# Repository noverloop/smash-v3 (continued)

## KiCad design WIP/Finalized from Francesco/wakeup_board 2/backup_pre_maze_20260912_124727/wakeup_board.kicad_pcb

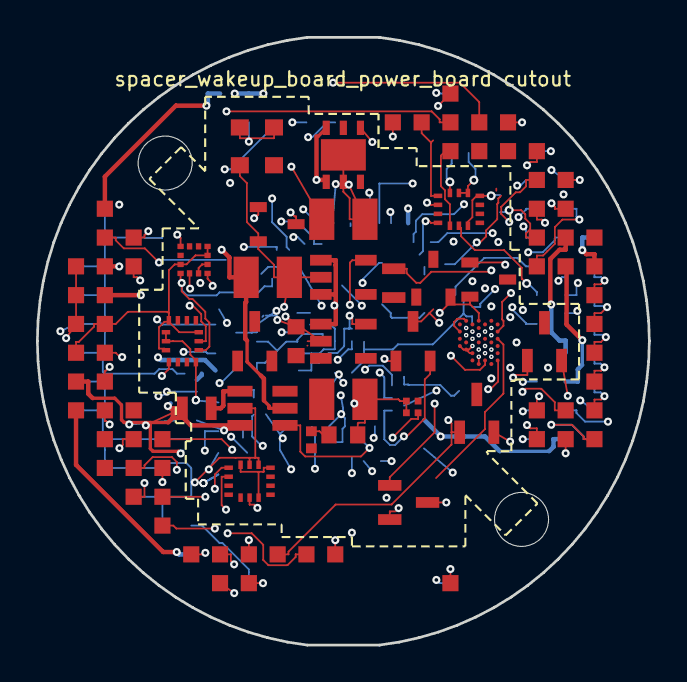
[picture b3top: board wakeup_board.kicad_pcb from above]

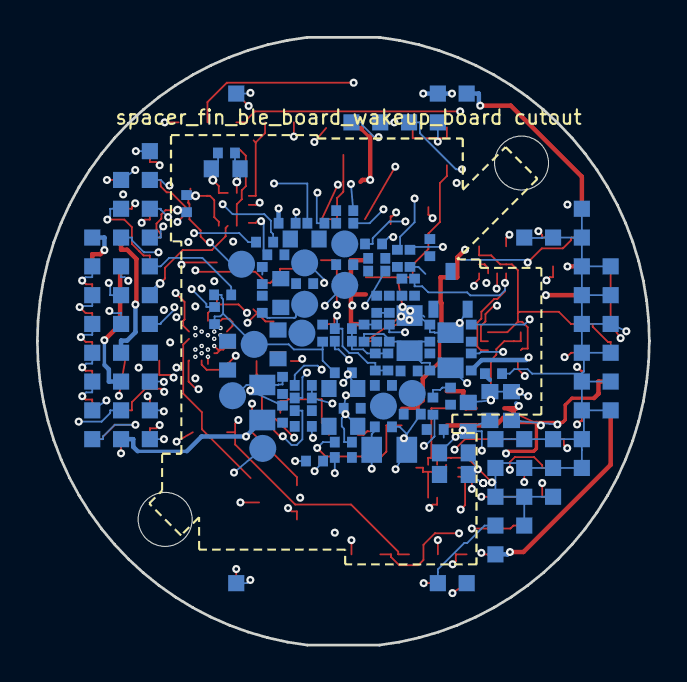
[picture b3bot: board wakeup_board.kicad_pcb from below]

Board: 14 copper layers, 34.0 x 33.8 mm, 112 parts (84 on the bottom side), 85 nets.

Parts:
CBOOST_IN1_1, CBOOST_IN1_2, CBOOST_IN1_3, CBOOST_IN1_4, CBOOST_IN1_5: C-Series MIL-PRF-32535 X7R 0603 2.2uF; Capacitor_SMD_C_0603_1608Metric
CBOOST_IN2: C0402 X7R 100nF; Capacitor_SMD_C_0402_1005Metric
CBOOST_OUT1: T491T 22uF (3528-12 thinnest variant); Capacitor_Tantalum_SMD_CP_EIA-3528-12_Kemet-T
CBOOST_OUT2: C0402 X7R 100nF; Capacitor_SMD_C_0402_1005Metric
CMAIN_HOLD: C0402 X7R 100nF; Capacitor_SMD_C_0402_1005Metric
COUT1, COUT2: T491T 22uF (3528-12 thinnest variant); Capacitor_Tantalum_SMD_CP_EIA-3528-12_Kemet-T
COUT3: C0402 X7R 100nF; Capacitor_SMD_C_0402_1005Metric
C_AON_IN: C-Series MIL-PRF-32535 X7R 0805 1uF; Capacitor_SMD_C_0805_2012Metric
C_AON_OUT: C-Series MIL-PRF-32535 X7R 0805 1uF; Capacitor_SMD_C_0805_2012Metric
C_CAM_VDD: C0402 X7R 100nF; Capacitor_SMD_C_0402_1005Metric
C_IMU1_1, C_IMU2_1, C_IMU3_1: C0402 X7R 100nF; Capacitor_SMD_C_0402_1005Metric
C_IMU1_2, C_IMU2_2, C_IMU3_2: C-Series MIL-PRF-32535 X7R 0603 2.2uF; Capacitor_SMD_C_0603_1608Metric
C_IMU1_3, C_IMU2_3, C_IMU3_3: C0402 X7R 10nF; Capacitor_SMD_C_0402_1005Metric
C_IR_WAKE: C0402 X7R 10nF; Capacitor_SMD_C_0402_1005Metric
C_MAG1: C0402 X7R 100nF; Capacitor_SMD_C_0402_1005Metric
C_MAG2: C-Series MIL-PRF-32535 X7R 0805 1uF; Capacitor_SMD_C_0805_2012Metric
C_MAG_C1: C-Series MIL-PRF-32535 X7R 0603 220nF; Capacitor_SMD_C_0603_1608Metric
C_MAG_SHELF: C0402 X7R 100nF; Capacitor_SMD_C_0402_1005Metric
C_MAG_WAKE: C0402 X7R 100nF; Capacitor_SMD_C_0402_1005Metric
C_TMR_LDO: C-Series MIL-PRF-32535 X7R 0805 1uF; Capacitor_SMD_C_0805_2012Metric
C_WBA_BULK_1, C_WBA_BULK_2: C-Series MIL-PRF-32535 X7R 0603 2.2uF; Capacitor_SMD_C_0603_1608Metric
C_WBA_HSE_VDD: C0402 X7R 100nF; Capacitor_SMD_C_0402_1005Metric
C_WBA_NRST: C0402 X7R 100nF; Capacitor_SMD_C_0402_1005Metric
C_WBA_PI1, C_WBA_PI2: SQCSVA 0.5pF; Capacitor_SMD_C_0603_1608Metric
C_WBA_VDD1, C_WBA_VDD2: C0402 X7R 100nF; Capacitor_SMD_C_0402_1005Metric
C_WBA_VDD11: C-Series MIL-PRF-32535 X7R 0603 2.2uF; Capacitor_SMD_C_0603_1608Metric
C_WBA_VDDA: C0402 X7R 100nF; Capacitor_SMD_C_0402_1005Metric
C_WBA_VDDANA: C0402 X7R 100nF; Capacitor_SMD_C_0402_1005Metric
C_WBA_VDDHPA: C0402 X7R 100nF; Capacitor_SMD_C_0402_1005Metric
C_WBA_VDDRF: C0402 X7R 100nF; Capacitor_SMD_C_0402_1005Metric
C_WBA_VDDRFPA: C0402 X7R 100nF; Capacitor_SMD_C_0402_1005Metric
C_WBA_VDDSMPS: C0402 X7R 100nF; Capacitor_SMD_C_0402_1005Metric
D_AON_WAKE: BAT64-06-TP; SOT95P237X125-3N
D_JUMP_WAKE: BAT64-06-TP; SOT95P237X125-3N
J_wakeup_board_spacer_wakeup_board_power_board: LGA_lands; J_wakeup_board_spacer_wakeup_board_power_board
L_PWR: TMS201210ALM-2R2MTAA; Inductor_SMD_L_2012_2.0x1.25mm
L_WBA_PI: WE-KI 0402 2.7nH (74479xxxxx family); Inductor_SMD_L_0402_1005Metric
L_WBA_SMPS: TMS201210ALM-2R2MTAA; Inductor_SMD_L_2012_2.0x1.25mm
P_wakeup_board_spacer_fin_ble_board_wakeup_board: LGA_lands; P_wakeup_board_spacer_fin_ble_board_wakeup_board
QHOLD, QHOLD2: BSS138LT1G; SOT96P237X111-3N
QMAIN: IRLML6402TRPBF; SOT95P237X112-3N
Q_AON_EN: IRLML6402TRPBF; SOT95P237X112-3N
Q_USB_WAKE2: BSS138LT1G; SOT96P237X111-3N
Q_WBA_RST: BSS138LT1G; SOT96P237X111-3N
RAON_PU: CRCW0402 1M 1% e3; Resistor_SMD_R_0402_1005Metric
RHOLD2_G: CRCW0402 100 1% e3; Resistor_SMD_R_0402_1005Metric
RHOLD2_PD: CRCW0402 100k 1% e3; Resistor_SMD_R_0402_1005Metric
RHOLD_AON: CRCW0402 1k 1% e3; Resistor_SMD_R_0402_1005Metric
RHOLD_G: CRCW0402 100 1% e3; Resistor_SMD_R_0402_1005Metric
RHOLD_PD: CRCW0402 100k 1% e3; Resistor_SMD_R_0402_1005Metric
RMAIN_PU: CRCW0402 1M 1% e3; Resistor_SMD_R_0402_1005Metric
RPU_I2C2_SCL, RPU_I2C2_SDA, RPU_I2C3_SCL, RPU_I2C3_SDA: CRCW0402 4.7k 1% e3; Resistor_SMD_R_0402_1005Metric
RPU_IR_WAKE: CRCW0402 470k 1% e3; Resistor_SMD_R_0402_1005Metric
RPU_MAG_WAKE: CRCW0402 1M 1% e3; Resistor_SMD_R_0402_1005Metric
RPU_SCL_EXT: CRCW0402 4.7k 1% e3; Resistor_SMD_R_0402_1005Metric
RPU_SDA_EXT: CRCW0402 4.7k 1% e3; Resistor_SMD_R_0402_1005Metric
R_BOOST_FB1: CRCW0402 220k 1% e3; Resistor_SMD_R_0402_1005Metric
R_BOOST_FB2: CRCW0402 100k 1% e3; Resistor_SMD_R_0402_1005Metric
R_IMU1_SCX_PU, R_IMU1_SDX_PU, R_IMU2_SCX_PU, R_IMU2_SDX_PU, R_IMU3_SCX_PU, R_IMU3_SDX_PU: CRCW0402 10k 1% e3; Resistor_SMD_R_0402_1005Metric
R_JUMP_PU: CRCW0402 22k 1% e3; Resistor_SMD_R_0402_1005Metric
R_JUMP_WAKE: CRCW0402 3.3k 1% e3; Resistor_SMD_R_0402_1005Metric
R_MAG_SHELF: CRCW0402 3.3k 1% e3; Resistor_SMD_R_0402_1005Metric
R_WBARST_PD: CRCW0402 100k 1% e3; Resistor_SMD_R_0402_1005Metric
R_WBA_BOOT0: CRCW0402 10k 1% e3; Resistor_SMD_R_0402_1005Metric
R_WBA_NRST: CRCW0402 10k 1% e3; Resistor_SMD_R_0402_1005Metric
R_WILK_ISO: CRCW0402 100 1% e3; Resistor_SMD_R_0402_1005Metric
TP_3V3: TP_3V3; TestPoint_TestPoint_Pad_D1.5mm
TP_BAT: TP_BAT; TestPoint_TestPoint_Pad_D1.5mm
TP_GND: TP_GND; TestPoint_TestPoint_Pad_D1.5mm
TP_IMU1_INT: TP_IMU1_INT; TestPoint_TestPoint_Pad_D1.5mm
TP_IMU2_INT: TP_IMU2_INT; TestPoint_TestPoint_Pad_D1.5mm
TP_IMU3_INT: TP_IMU3_INT; TestPoint_TestPoint_Pad_D1.5mm
TP_MAG_DRDY: TP_MAG_DRDY; TestPoint_TestPoint_Pad_D1.5mm
TP_WILK_A: TP_WILK_A; TestPoint_TestPoint_Pad_D1.5mm
TP_WILK_B: TP_WILK_B; TestPoint_TestPoint_Pad_D1.5mm
TP_YAGI_RF_A: TP_YAGI_RF_A; TestPoint_TestPoint_Pad_D1.5mm
TP_YAGI_RF_B: TP_YAGI_RF_B; TestPoint_TestPoint_Pad_D1.5mm
U_AON_LDO: TPS7A0233PDBVR; SOT95P280X145-5N
U_BOOST: MCP1640CT-I/CHY; SOT95P270X145-6N
U_IMU1, U_IMU2, U_IMU3: ISM330DHCXTR; LSM6DS3USTR (LGA-14)
U_MAG: IIS2MDCTR
U_MAG_SHELF: RR123-1H02-612
U_MAG_WAKE: SOT95P237X112-3N
U_PWR: LDL112PV33R; SON95P300X300X100-7N-D
U_TMR_LDO: TPS7A0233PDBVR; SOT95P280X145-5N
U_WBA: STM32WBA55HGF6TR; BGA41C35P13X7_298X276X50
Y_WBA_HSE: DSC1001CI5-032.0000; DSC1001CI50080000

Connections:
3V3: COUT1.1, COUT2.1, COUT3.1, C_IMU1_1.1, C_IMU1_2.1, C_IMU1_3.1, C_IMU2_1.1, C_IMU2_2.1, C_IMU2_3.1, C_IMU3_1.1, C_IMU3_2.1, C_IMU3_3.1, C_MAG1.1, C_MAG2.1, J_wakeup_board_spacer_wakeup_board_powe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.1, J_wakeup_board_spacer_wakeup_board_powe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.55, J_wakeup_board_spacer_wakeup_board_powe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.62, P_wakeup_board_spacer_fin_ble_board_wak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.1, P_wakeup_board_spacer_fin_ble_board_wak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.35, P_wakeup_board_spacer_fin_ble_board_wak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.41, RPU_I2C2_SCL.1, RPU_I2C2_SDA.1, RPU_I2C3_SCL.1, RPU_I2C3_SDA.1, RPU_SCL_EXT.1, RPU_SDA_EXT.1, R_IMU1_SCX_PU.1, R_IMU1_SDX_PU.1, R_IMU2_SCX_PU.1, R_IMU2_SDX_PU.1, R_IMU3_SCX_PU.1, R_IMU3_SDX_PU.1, TP_3V3.1, U_IMU1.5, U_IMU1.8, U_IMU1.12, U_IMU2.5, U_IMU2.8, U_IMU2.12, U_IMU3.1, U_IMU3.5, U_IMU3.8, U_IMU3.12, U_MAG.3, U_MAG.9, U_MAG.10, U_PWR.4
3V3_AON: C_AON_OUT.1, C_MAG_WAKE.1, C_WBA_BULK_1.1, C_WBA_BULK_2.1, C_WBA_HSE_VDD.1, C_WBA_VDD1.1, C_WBA_VDD2.1, C_WBA_VDDA.1, C_WBA_VDDANA.1, C_WBA_VDDHPA.1, C_WBA_VDDRF.1, C_WBA_VDDRFPA.1, C_WBA_VDDSMPS.1, P_wakeup_board_spacer_fin_ble_board_wak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.2, P_wakeup_board_spacer_fin_ble_board_wak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.36, RPU_IR_WAKE.1, RPU_MAG_WAKE.1, R_WBA_NRST.1, U_AON_LDO.5, U_MAG_WAKE.1, U_WBA.A6, U_WBA.A10, U_WBA.B5, U_WBA.B13, U_WBA.C4, U_WBA.C6, U_WBA.E12, U_WBA.G4, Y_WBA_HSE.1, Y_WBA_HSE.4
ACTIVATE_CONFIRM: J_wakeup_board_spacer_wakeup_board_powe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.2, P_wakeup_board_spacer_fin_ble_board_wak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.3
ACTIVATE_SET: J_wakeup_board_spacer_wakeup_board_powe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.3, P_wakeup_board_spacer_fin_ble_board_wak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.4
AON_EN: Q_AON_EN.3, RHOLD_AON.2, U_AON_LDO.3
AON_EN_GATE: D_AON_WAKE.3, Q_AON_EN.1, Q_USB_WAKE2.3, RAON_PU.2
BAT_CELL1_POS: J_wakeup_board_spacer_wakeup_board_powe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.4, P_wakeup_board_spacer_fin_ble_board_wak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.5
BAT_CELL2_POS: J_wakeup_board_spacer_wakeup_board_powe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.5, P_wakeup_board_spacer_fin_ble_board_wak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.6
BAT_CELL3_POS: J_wakeup_board_spacer_wakeup_board_powe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.6, P_wakeup_board_spacer_fin_ble_board_wak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.7
BAT_PROT: J_wakeup_board_spacer_wakeup_board_powe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.7, J_wakeup_board_spacer_wakeup_board_powe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.56, P_wakeup_board_spacer_fin_ble_board_wak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.8, P_wakeup_board_spacer_fin_ble_board_wak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.37, QMAIN.2, TP_BAT.1
BAT_RAW: C_AON_IN.1, J_wakeup_board_spacer_wakeup_board_powe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.8, J_wakeup_board_spacer_wakeup_board_powe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.57, P_wakeup_board_spacer_fin_ble_board_wak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.9, P_wakeup_board_spacer_fin_ble_board_wak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.38, Q_AON_EN.2, RAON_PU.1, RMAIN_PU.1, R_JUMP_PU.1, U_AON_LDO.1, U_TMR_LDO.1, U_TMR_LDO.3
BOOST_FB: R_BOOST_FB1.2, R_BOOST_FB2.1, U_BOOST.4
BOOST_OUT: CBOOST_OUT1.1, CBOOST_OUT2.1, R_BOOST_FB1.1, U_BOOST.5, U_PWR.1, U_PWR.6
BOOST_SW: L_PWR.2, U_BOOST.1
BOOT0: J_wakeup_board_spacer_wakeup_board_powe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.9, P_wakeup_board_spacer_fin_ble_board_wak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.10
COMP_1V8: C_CAM_VDD.1, J_wakeup_board_spacer_wakeup_board_powe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.10, J_wakeup_board_spacer_wakeup_board_powe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.58
COMP_5V: J_wakeup_board_spacer_wakeup_board_powe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.11, J_wakeup_board_spacer_wakeup_board_powe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.59, P_wakeup_board_spacer_fin_ble_board_wak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.11, P_wakeup_board_spacer_fin_ble_board_wak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.39
COMP_5V_RAW: J_wakeup_board_spacer_wakeup_board_powe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.12, J_wakeup_board_spacer_wakeup_board_powe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.60, P_wakeup_board_spacer_fin_ble_board_wak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.12, P_wakeup_board_spacer_fin_ble_board_wak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.40
COMP_OUT: J_wakeup_board_spacer_wakeup_board_powe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.13, P_wakeup_board_spacer_fin_ble_board_wak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.13
COMP_SWDCLK: J_wakeup_board_spacer_wakeup_board_powe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.14, P_wakeup_board_spacer_fin_ble_board_wak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.14
COMP_SWDIO: J_wakeup_board_spacer_wakeup_board_powe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.15, P_wakeup_board_spacer_fin_ble_board_wak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.15
EXT_CAN_RX: J_wakeup_board_spacer_wakeup_board_powe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.16, P_wakeup_board_spacer_fin_ble_board_wak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.16
EXT_CAN_TX: J_wakeup_board_spacer_wakeup_board_powe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.17, P_wakeup_board_spacer_fin_ble_board_wak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.17
FLEX_GND: CBOOST_IN1_1.2, CBOOST_IN1_2.2, CBOOST_IN1_3.2, CBOOST_IN1_4.2, CBOOST_IN1_5.2, CBOOST_IN2.2, CBOOST_OUT1.2, CBOOST_OUT2.2, CMAIN_HOLD.2, COUT1.2, COUT2.2, COUT3.2, C_AON_IN.2, C_AON_OUT.2, C_CAM_VDD.2, C_IMU1_1.2, C_IMU1_2.2, C_IMU1_3.2, C_IMU2_1.2, C_IMU2_2.2, C_IMU2_3.2, C_IMU3_1.2, C_IMU3_2.2, C_IMU3_3.2, C_IR_WAKE.2, C_MAG1.2, C_MAG2.2, C_MAG_C1.2, C_MAG_SHELF.2, C_MAG_WAKE.2, C_TMR_LDO.2, C_WBA_BULK_1.2, C_WBA_BULK_2.2, C_WBA_HSE_VDD.2, C_WBA_NRST.2, C_WBA_PI1.2, C_WBA_PI2.2, C_WBA_VDD1.2, C_WBA_VDD2.2, C_WBA_VDD11.2, C_WBA_VDDA.2, C_WBA_VDDANA.2, C_WBA_VDDHPA.2, C_WBA_VDDRF.2, C_WBA_VDDRFPA.2, C_WBA_VDDSMPS.2, J_wakeup_board_spacer_wakeup_board_powe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.18, J_wakeup_board_spacer_wakeup_board_powe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.63, J_wakeup_board_spacer_wakeup_board_powe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.64, J_wakeup_board_spacer_wakeup_board_powe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.65, P_wakeup_board_spacer_fin_ble_board_wak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.18, P_wakeup_board_spacer_fin_ble_board_wak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.42, P_wakeup_board_spacer_fin_ble_board_wak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.43, P_wakeup_board_spacer_fin_ble_board_wak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.44, P_wakeup_board_spacer_fin_ble_board_wak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.45, P_wakeup_board_spacer_fin_ble_board_wak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.46, P_wakeup_board_spacer_fin_ble_board_wak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.47, P_wakeup_board_spacer_fin_ble_board_wak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.48, P_wakeup_board_spacer_fin_ble_board_wak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.49, P_wakeup_board_spacer_fin_ble_board_wak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.50, P_wakeup_board_spacer_fin_ble_board_wak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.51, P_wakeup_board_spacer_fin_ble_board_wak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.52, P_wakeup_board_spacer_fin_ble_board_wak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.53, P_wakeup_board_spacer_fin_ble_board_wak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.54, P_wakeup_board_spacer_fin_ble_board_wak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.55, P_wakeup_board_spacer_fin_ble_board_wak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.56, P_wakeup_board_spacer_fin_ble_board_wak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.57, P_wakeup_board_spacer_fin_ble_board_wak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.58, P_wakeup_board_spacer_fin_ble_board_wak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.59, P_wakeup_board_spacer_fin_ble_board_wak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.60, P_wakeup_board_spacer_fin_ble_board_wak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.61, P_wakeup_board_spacer_fin_ble_board_wak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.62, P_wakeup_board_spacer_fin_ble_board_wak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.63, P_wakeup_board_spacer_fin_ble_board_wak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.64, P_wakeup_board_spacer_fin_ble_board_wak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.65, P_wakeup_board_spacer_fin_ble_board_wak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.66, P_wakeup_board_spacer_fin_ble_board_wak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.67, P_wakeup_board_spacer_fin_ble_board_wak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.68, P_wakeup_board_spacer_fin_ble_board_wak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.69, QHOLD.2, QHOLD2.2, Q_USB_WAKE2.2, Q_WBA_RST.2, RHOLD2_PD.2, RHOLD_PD.2, R_BOOST_FB2.2, R_WBARST_PD.2, R_WBA_BOOT0.2, TP_GND.1, U_AON_LDO.2, U_BOOST.2, U_IMU1.1, U_IMU1.6, U_IMU1.7, U_IMU2.1, U_IMU2.6, U_IMU2.7, U_IMU3.6, U_IMU3.7, U_MAG.6, U_MAG.8, U_MAG_SHELF.1, U_MAG_SHELF.4, U_MAG_WAKE.3, U_PWR.2, U_PWR.7, U_TMR_LDO.2, U_WBA.A12, U_WBA.B9, U_WBA.D1, U_WBA.D3, U_WBA.D5, U_WBA.D13, U_WBA.G6, Y_WBA_HSE.2
GPIO_EXT_0: J_wakeup_board_spacer_wakeup_board_powe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.19, P_wakeup_board_spacer_fin_ble_board_wak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.19
GPIO_EXT_1: J_wakeup_board_spacer_wakeup_board_powe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.20, P_wakeup_board_spacer_fin_ble_board_wak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.20
GPIO_EXT_2: J_wakeup_board_spacer_wakeup_board_powe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.21, P_wakeup_board_spacer_fin_ble_board_wak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.21
GPIO_EXT_3: J_wakeup_board_spacer_wakeup_board_powe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.22, P_wakeup_board_spacer_fin_ble_board_wak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.22
H3LIS_INT1: J_wakeup_board_spacer_wakeup_board_powe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.23, P_wakeup_board_spacer_fin_ble_board_wak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.23
I2C2_SCL: J_wakeup_board_spacer_wakeup_board_powe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.24, RPU_I2C2_SCL.2, U_IMU1.13, U_MAG.1, U_WBA.F3
I2C2_SDA: J_wakeup_board_spacer_wakeup_board_powe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.25, RPU_I2C2_SDA.2, U_IMU1.14, U_MAG.4, U_WBA.G2
I2C3_SCL: J_wakeup_board_spacer_wakeup_board_powe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.26, P_wakeup_board_spacer_fin_ble_board_wak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.24, RPU_I2C3_SCL.2, U_IMU2.13, U_IMU3.13
I2C3_SDA: J_wakeup_board_spacer_wakeup_board_powe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.27, P_wakeup_board_spacer_fin_ble_board_wak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.25, RPU_I2C3_SDA.2, U_IMU2.14, U_IMU3.14
IMU1_INT: J_wakeup_board_spacer_wakeup_board_powe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.28, TP_IMU1_INT.1, U_IMU1.4
IMU1_SCX: R_IMU1_SCX_PU.2, U_IMU1.3
IMU1_SDX: R_IMU1_SDX_PU.2, U_IMU1.2
IMU2_INT: J_wakeup_board_spacer_wakeup_board_powe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.29, TP_IMU2_INT.1, U_IMU2.4
IMU2_SCX: R_IMU2_SCX_PU.2, U_IMU2.3
IMU2_SDX: R_IMU2_SDX_PU.2, U_IMU2.2
IMU3_INT: J_wakeup_board_spacer_wakeup_board_powe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.30, TP_IMU3_INT.1, U_IMU3.4
IMU3_SCX: R_IMU3_SCX_PU.2, U_IMU3.3
IMU3_SDX: R_IMU3_SDX_PU.2, U_IMU3.2
IR_TX: J_wakeup_board_spacer_wakeup_board_powe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.31, U_WBA.D9
IR_WAKE: C_IR_WAKE.1, J_wakeup_board_spacer_wakeup_board_powe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.32, RPU_IR_WAKE.2, U_WBA.E6
JUMP_WAKE: P_wakeup_board_spacer_fin_ble_board_wak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.26, R_JUMP_PU.2, R_JUMP_WAKE.2
JUMP_WAKE_K: D_AON_WAKE.1, D_JUMP_WAKE.1, R_JUMP_WAKE.1
MAG_C1_TERM: C_MAG_C1.1, U_MAG.5
MAG_DRDY: J_wakeup_board_spacer_wakeup_board_powe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.33, TP_MAG_DRDY.1, U_MAG.7
MAG_SHELF_K: D_AON_WAKE.2, D_JUMP_WAKE.2, R_MAG_SHELF.1
MAG_SHELF_N: R_MAG_SHELF.2, U_MAG_SHELF.3
MAG_WAKE_N: RPU_MAG_WAKE.2, U_MAG_WAKE.2, U_WBA.G8
MAIN_SW_GATE: CMAIN_HOLD.1, D_JUMP_WAKE.3, J_wakeup_board_spacer_wakeup_board_powe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.34, QHOLD.3, QHOLD2.3, QMAIN.1, RMAIN_PU.2
NRST: J_wakeup_board_spacer_wakeup_board_powe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.35, P_wakeup_board_spacer_fin_ble_board_wak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.27
PWR_HOLD: J_wakeup_board_spacer_wakeup_board_powe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.36, RHOLD_G.1
QHOLD2_GATE: QHOLD2.1, RHOLD2_G.2, RHOLD2_PD.1
QHOLD_GATE: QHOLD.1, RHOLD_G.2, RHOLD_PD.1
REG_IN_MAIN: CBOOST_IN1_1.1, CBOOST_IN1_2.1, CBOOST_IN1_3.1, CBOOST_IN1_4.1, CBOOST_IN1_5.1, CBOOST_IN2.1, J_wakeup_board_spacer_wakeup_board_powe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.37, J_wakeup_board_spacer_wakeup_board_powe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.61, L_PWR.1, QMAIN.3, U_BOOST.3, U_BOOST.6
SWO: J_wakeup_board_spacer_wakeup_board_powe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.38, P_wakeup_board_spacer_fin_ble_board_wak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.28
SYS_I2C_SCL: J_wakeup_board_spacer_wakeup_board_powe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.39, P_wakeup_board_spacer_fin_ble_board_wak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.29, RPU_SCL_EXT.2
SYS_I2C_SDA: J_wakeup_board_spacer_wakeup_board_powe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.40, P_wakeup_board_spacer_fin_ble_board_wak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.30, RPU_SDA_EXT.2
SYS_SPI_CS_FIN: J_wakeup_board_spacer_wakeup_board_powe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.41, P_wakeup_board_spacer_fin_ble_board_wak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.31
SYS_SPI_MISO: J_wakeup_board_spacer_wakeup_board_powe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.42, P_wakeup_board_spacer_fin_ble_board_wak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.32
SYS_SPI_MOSI: J_wakeup_board_spacer_wakeup_board_powe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.43, P_wakeup_board_spacer_fin_ble_board_wak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.33
SYS_SPI_SCLK: J_wakeup_board_spacer_wakeup_board_powe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.44, P_wakeup_board_spacer_fin_ble_board_wak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.34
TMR_VDD: C_MAG_SHELF.1, C_TMR_LDO.1, U_MAG_SHELF.2, U_TMR_LDO.5
USBWK_GATE: J_wakeup_board_spacer_wakeup_board_powe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.45, Q_USB_WAKE2.1
WBA_AON_HOLD: RHOLD_AON.1, U_WBA.E4
WBA_BOOT0: J_wakeup_board_spacer_wakeup_board_powe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.46, R_WBA_BOOT0.1, U_WBA.C8
WBA_HCI_IRQ: J_wakeup_board_spacer_wakeup_board_powe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.47, U_WBA.C10
WBA_HCI_MISO: J_wakeup_board_spacer_wakeup_board_powe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.48, U_WBA.F9
WBA_HCI_MOSI: J_wakeup_board_spacer_wakeup_board_powe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.49, U_WBA.G10
WBA_HCI_NSS: J_wakeup_board_spacer_wakeup_board_powe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.50, U_WBA.F13
WBA_HCI_SCK: J_wakeup_board_spacer_wakeup_board_powe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.51, U_WBA.G12
WBA_HSE_IN: U_WBA.A8, Y_WBA_HSE.3
WBA_NRST: C_WBA_NRST.1, Q_WBA_RST.3, R_WBA_NRST.2, U_WBA.E2
WBA_RF: C_WBA_PI1.1, L_WBA_PI.1, U_WBA.C2
WBA_RF_M: C_WBA_PI2.1, L_WBA_PI.2
WBA_RST_CMD: J_wakeup_board_spacer_wakeup_board_powe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.52, Q_WBA_RST.1, R_WBARST_PD.1
WBA_UART_RX: J_wakeup_board_spacer_wakeup_board_powe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.53, U_WBA.E10
WBA_UART_TX: J_wakeup_board_spacer_wakeup_board_powe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.54, U_WBA.F11
WBA_VDD11: C_WBA_VDD11.1, L_WBA_SMPS.2, U_WBA.B11
WBA_VLX: L_WBA_SMPS.1, U_WBA.C12
WBA_WAKE: RHOLD2_G.1, U_WBA.F5
YAGI_WILK_A: R_WILK_ISO.1, TP_WILK_A.1
YAGI_WILK_B: R_WILK_ISO.2, TP_WILK_B.1
